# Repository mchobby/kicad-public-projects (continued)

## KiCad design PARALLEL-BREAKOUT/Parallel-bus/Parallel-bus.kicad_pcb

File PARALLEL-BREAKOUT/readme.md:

# Parallel-Breakout retro development project with Linux & Python

## A bit a history

I wanted to re-discover __Parallel port development__ on older computer with Python (see [Dell Optiplex GX260](https://arduino103.blogspot.com/search?q=optiplex) and [HP NC6000](https://arduino103.blogspot.com/search?q=nc6000) salvage).

Those are quite old computers as the OPtiplex is date from 2002 (2007 for the NC6000) and I wanted to used more modern operating system for development.

[Linux Bionic Puppy and Fossa Puppy](https://puppylinux-woof-ce.github.io/) (derivated from Ubuntu Linux) does a really great job to modernise the operating system.

## Browsing sub-projects

This project is made of many sub-project. Just navigates the various sub-folder to gets more information about them. I stored readme files into each sub-folder to give some details about that part of the project.

The main sub-projects are:
* [Parallel-brk](Parallel-brk): breakout a parallel port to a RPi GPIO alike port.
* [Parallel-cobbler](Parallel-cobbler): from GPIO to breadboard converted.  
* [Parallel-bus](Parallel-bus): from GPIO to 16bits address bus + 8bits data bus + clock + control bus.  

# Prototyping Hardware
From there, I started to design 2 first boards to facilitate test and prototyping.

The board are shares in the following sub-directories, __please keep the credit__:

* [Parallel-brk](Parallel-brk) : breakouts the Parallel port to a 2x20 connector (like Raspberry-Pi) and inject 3.3 + 5V at the right place on the GPIOs
* [Parallel-cobbler](Parallel-cobbler) : translate the 2x20 pinout to a prototyping Cobbler. Cobbler  a board that can be plugged onto a breadboard to make prototyping. The 5V and 3.3V are also available on the breakout so we are ready to prototype stuff!

__/!\ 5V Logic /!\__ warning the parallel port is 5V logic only!

## Installing pyparallel

Developping parallel port stuff with Python would requires to install the `pyparallel` package.

We have described the __python3-parallel__ (0.2.2-2) ["Linux Package Installation" in this article](https://arduino103.blogspot.com/2022/06/recuperation-dell-optiplex-gx260n-et_01622143827.html) to support PyParallel on my Linux Puppy (still written in french, ask google for translation)

## Inital Input/Output test

The article "[Parallel Breakout: test d'entrée/sortie en python](https://arduino103.blogspot.com/2022/07/parallel-breakout-tests-dentreesorties.html)" (Google may help to translate) shows how to wire input and outpout on the breakout and how to drive them from Python.

The Parallel port do have 8 output data bit (D0..D7).

The parallel port also brings 5 inputs bits and 4 additional output bits (C0..C4 that can be switched to input... but not recommended).

The Python code is [available here](https://arduino103.blogspot.com/2022/07/parallel-breakout-tests-dentreesorties.html).

# Expand parallel port to data & address bus

Read more from the [Parallel-bus sub-project folder](Parallel-bus/)

# Ressources
* [All the "Parallel-Breakout" articles available on the blog](https://arduino103.blogspot.com/search?q=parallel-breakout) (_french_)

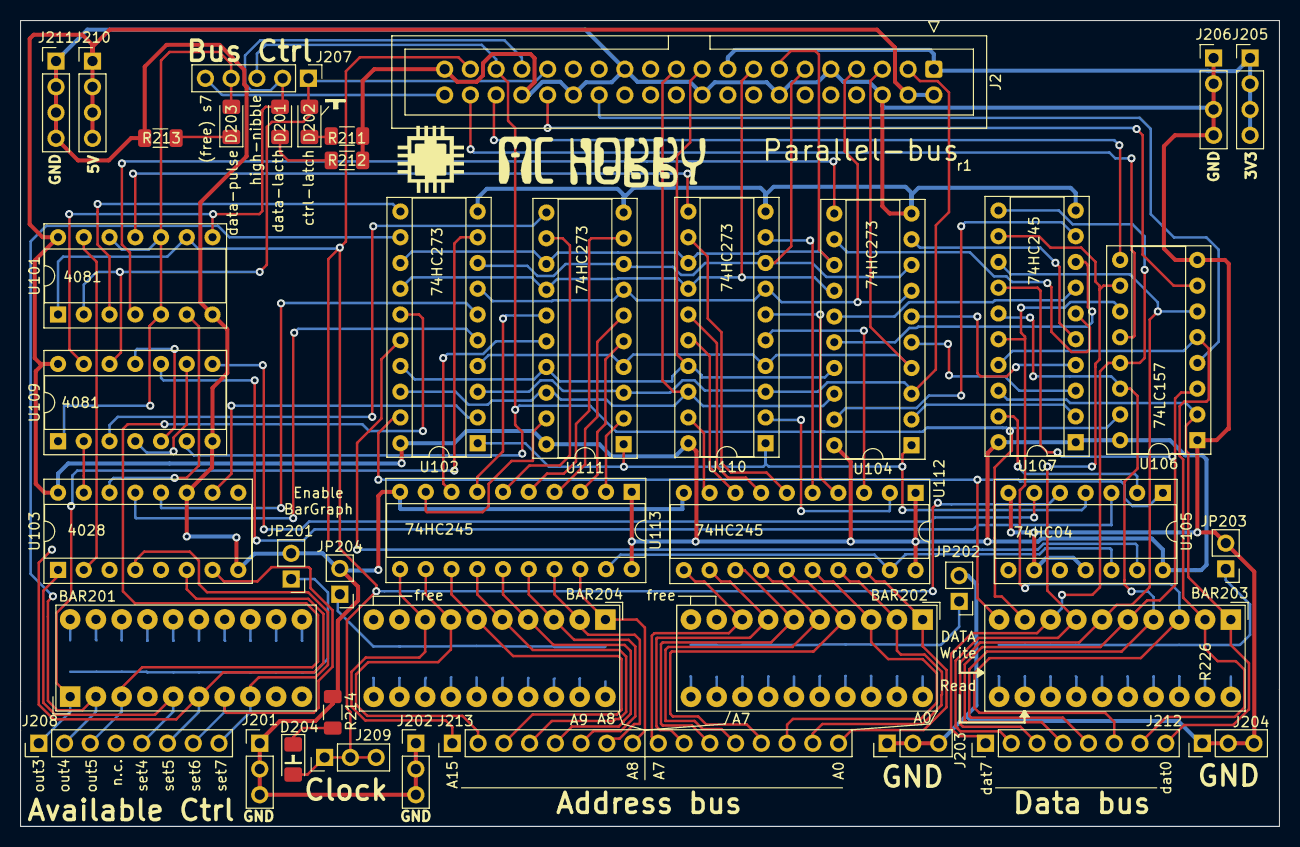
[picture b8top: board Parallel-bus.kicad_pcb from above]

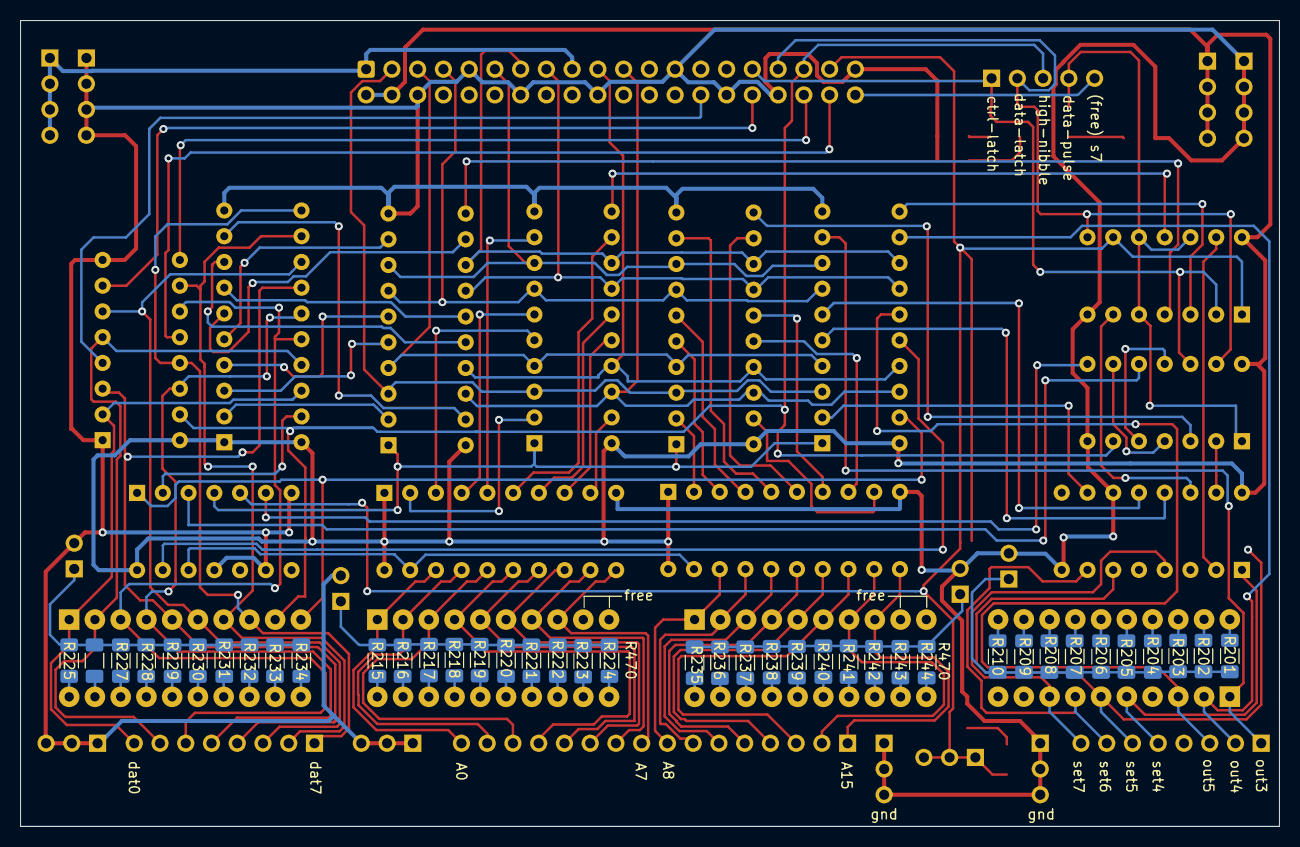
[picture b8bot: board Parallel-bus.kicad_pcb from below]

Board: 2 copper layers, 124.2 x 79.5 mm, 82 parts (40 on the bottom side), 143 nets.

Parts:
BAR201: Bar_Avail_bits; HDSP-4830
BAR202: Bar_Addr_L; HDSP-4830
BAR203: Bar_Data_bus; HDSP-4830
BAR204: Bar_Addr_H; HDSP-4830
D201: LED_Data_Latch; LED_1206_3216Metric_Pad1.42x1.75mm_HandSolder
D202: LED_Ctrl_Latch; LED_1206_3216Metric_Pad1.42x1.75mm_HandSolder
D203, D204: LED_Data_Pulse; LED_1206_3216Metric_Pad1.42x1.75mm_HandSolder
J2: Conn_RASP; IDC-Header_2x20_P2.54mm_Vertical
J201: Conn_GND0; PinHeader_1x03_P2.54mm_Vertical
J202: Conn_GND1; PinHeader_1x03_P2.54mm_Vertical
J203: Conn_GND2; PinHeader_1x03_P2.54mm_Vertical
J204: Conn_GND3; PinHeader_1x03_P2.54mm_Vertical
J205: Conn_3V; PinHeader_1x04_P2.54mm_Vertical
J206: Conn_GND4; PinHeader_1x04_P2.54mm_Vertical
J207: Conn_Bus_Ctrl; PinHeader_1x05_P2.54mm_Vertical
J208: Conn_Avail_Ctrl; PinHeader_1x08_P2.54mm_Vertical
J209: Conn_clock; PinHeader_1x03_P2.54mm_Vertical
J210: Conn_5V; PinHeader_1x04_P2.54mm_Vertical
J211: Conn_GND5; PinHeader_1x04_P2.54mm_Vertical
J212: Conn_Data_bus; PinHeader_1x08_P2.54mm_Vertical
J213: Conn_Addr_bus; PinHeader_1x16_P2.54mm_Vertical
JP201, JP203: Jumper; PinHeader_1x02_P2.54mm_Vertical
JP202: Addr-L; PinHeader_1x02_P2.54mm_Vertical
JP204: Addr-H; PinHeader_1x02_P2.54mm_Vertical
R201, R202, R203, R204, R205, R206, R207, R208, R209, R210, R211, R212, R213, R214, R215, R216, R217, R218, R219, R220, R221, R222, R223, R224, R225, R226, R227, R228, R229, R230, R231, R232, R233, R234, R235, R236, R237, R238, R239, R240, R241, R242, R243, R244: R470; R_1206_3216Metric_Pad1.30x1.75mm_HandSolder
U101, U109: 4081; DIP-14_W7.62mm_Socket
U102, U104, U110, U111: 74HC273; DIP-20_W7.62mm_Socket
U103: 4028; DIP-16_W7.62mm_Socket
U105: 74HC04; DIP-14_W7.62mm_Socket
U106: 74LS157; DIP-16_W7.62mm_Socket
U107, U112, U113: 74HC245; DIP-20_W7.62mm_Socket

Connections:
+3V3: J2.1, J2.17, J205.1, J205.2, J205.3, J205.4
+5V: J2.2, J2.4, J210.1, J210.2, J210.3, J210.4, U101.14, U102.20, U103.16, U104.20, U105.14, U106.16, U107.1, U107.20, U109.14, U110.20, U111.20, U112.1, U112.20, U113.1, U113.20
/addr-h-set: U103.15, U109.2
/addr-l-set: U101.13, U103.2
/addr-out: U102.16, U105.13
/d0: J2.3, U102.3, U104.3, U110.3, U111.3
/d1: J2.5, U102.4, U104.4, U110.4, U111.4
/d2: J2.7, U102.7, U104.7, U110.7, U111.7
/d3: J2.11, U102.8, U104.8, U110.8, U111.8
/d4: J2.13, U102.13, U104.13, U110.13, U111.13
/d5: J2.15, U102.14, U104.14, U110.14, U111.14
/d6: J2.19, U102.17, U104.17, U110.17, U111.17
/d7: J2.21, U102.18, U104.18, U110.18, U111.18
/data-set: U101.6, U103.14
/s3: J2.28, U106.4
/s4: J2.32, U106.7
/s5: J2.36, U106.9
/s6: J2.38, U106.12
GND: J2.6, J2.9, J2.14, J2.20, J2.25, J2.30, J2.34, J2.39, J201.1, J201.2, J201.3, J202.1, J202.2, J202.3, J203.1, J203.2, J203.3, J204.1, J204.2, J204.3, J206.1, J206.2, J206.3, J206.4, J211.1, J211.2, J211.3, J211.4, JP201.2, JP202.2, JP203.2, JP204.2, R211.1, R212.1, R213.1, R214.1, U101.7, U102.10, U103.8, U103.11, U104.10, U105.7, U105.9, U105.11, U106.1, U106.8, U107.10, U109.7, U110.10, U111.10, U112.10, U113.10
unnamed: BAR201.11, R210.2
unnamed: BAR201.12, R209.2
unnamed: BAR201.13, R208.2
unnamed: BAR201.14, R207.2
unnamed: BAR201.15, R206.2
unnamed: BAR201.16, R205.2
unnamed: BAR201.17, R204.2
unnamed: BAR201.18, R203.2
unnamed: BAR201.19, R202.2
unnamed: BAR201.20, R201.2
unnamed: BAR202.11, R224.2
unnamed: BAR202.12, R223.2
unnamed: BAR202.13, R222.2
unnamed: BAR202.14, R221.2
unnamed: BAR202.15, R220.2
unnamed: BAR202.16, R219.2
unnamed: BAR202.17, R218.2
unnamed: BAR202.18, R217.2
unnamed: BAR202.19, R216.2
unnamed: BAR202.20, R215.2
unnamed: BAR203.11, R234.2
unnamed: BAR203.12, R233.2
unnamed: BAR203.13, R232.2
unnamed: BAR203.14, R231.2
unnamed: BAR203.15, R230.2
unnamed: BAR203.16, R229.2
unnamed: BAR203.17, R228.2
unnamed: BAR203.18, R227.2
unnamed: BAR203.19, R226.2
unnamed: BAR203.20, R225.2
unnamed: BAR204.11, R244.2
unnamed: BAR204.12, R243.2
unnamed: BAR204.13, R242.2
unnamed: BAR204.14, R241.2
unnamed: BAR204.15, R240.2
unnamed: BAR204.16, R239.2
unnamed: BAR204.17, R238.2
unnamed: BAR204.18, R237.2
unnamed: BAR204.19, R236.2
unnamed: BAR204.20, R235.2
unnamed: D201.1, R212.2
unnamed: D202.1, R211.2
unnamed: D203.1, R213.2
unnamed: D204.1, R214.2
unnamed: JP201.1, R201.1, R202.1, R203.1, R204.1, R205.1, R206.1, R207.1, R208.1, R209.1, R210.1
unnamed: JP202.1, R215.1, R216.1, R217.1, R218.1, R219.1, R220.1, R221.1, R222.1, R223.1, R224.1
unnamed: JP203.1, R225.1, R226.1, R227.1, R228.1, R229.1, R230.1, R231.1, R232.1, R233.1, R234.1
unnamed: JP204.1, R235.1, R236.1, R237.1, R238.1, R239.1, R240.1, R241.1, R242.1, R243.1, R244.1
unnamed: U101.3, U102.11
unnamed: U101.4, U104.11
unnamed: U101.11, U110.11
unnamed: U102.2, U103.10
unnamed: U102.5, U103.13
unnamed: U102.6, U103.12
unnamed: U104.2, U107.2
unnamed: U104.5, U107.3
unnamed: U104.6, U107.4
unnamed: U104.9, U107.5
unnamed: U104.12, U107.6
unnamed: U104.15, U107.7
unnamed: U104.16, U107.8
unnamed: U104.19, U107.9
unnamed: U105.2, U107.19
unnamed: U105.3, U109.10
unnamed: U105.6, U109.8
unnamed: U105.12, U112.19, U113.19
unnamed: U109.3, U111.11
unnamed: U109.4, U109.9
unnamed: U109.5, U109.11
unnamed: U110.2, U112.2
unnamed: U110.5, U112.3
unnamed: U110.6, U112.4
unnamed: U110.9, U112.5
unnamed: U110.12, U112.6
unnamed: U110.15, U112.7
unnamed: U110.16, U112.8
unnamed: U110.19, U112.9
unnamed: U111.2, U113.2
unnamed: U111.5, U113.3
unnamed: U111.6, U113.4
unnamed: U111.9, U113.5
unnamed: U111.12, U113.6
unnamed: U111.15, U113.7
unnamed: U111.16, U113.8
unnamed: U111.19, U113.9
adr0: BAR202.1, J213.16, U112.18
adr1: BAR202.2, J213.15, U112.17
adr2: BAR202.3, J213.14, U112.16
adr3: BAR202.4, J213.13, U112.15
adr4: BAR202.5, J213.12, U112.14
adr5: BAR202.6, J213.11, U112.13
adr6: BAR202.7, J213.10, U112.12
adr7: BAR202.8, J213.9, U112.11
adr8: BAR204.1, J213.8, U113.18
adr9: BAR204.2, J213.7, U113.17
adr10: BAR204.3, J213.6, U113.16
adr11: BAR204.4, J213.5, U113.15
adr12: BAR204.5, J213.4, U113.14
adr13: BAR204.6, J213.3, U113.13
adr14: BAR204.7, J213.2, U113.12
adr15: BAR204.8, J213.1, U113.11
clock: D204.2, J2.37, J209.1, J209.2, J209.3, U101.1, U101.9, U105.5
ctrl-latch: D202.2, J2.31, J207.1, U101.2, U109.12
dat0: BAR203.1, J212.8, U106.2, U107.18
dat1: BAR203.2, J212.7, U106.5, U107.17
dat2: BAR203.3, J212.6, U106.11, U107.16
dat3: BAR203.4, J212.5, U106.14, U107.15
dat4: BAR203.5, J212.4, U106.3, U107.14
dat5: BAR203.6, J212.3, U106.6, U107.13
dat6: BAR203.7, J212.2, U106.10, U107.12
dat7: BAR203.8, J212.1, U106.13, U107.11
data-latch: D201.2, J2.33, J207.2, U101.8, U109.13
data-out: BAR203.10, U102.19, U105.1
data-pulse: D203.2, J207.4, U101.5, U101.10, U101.12, U109.1
high-nibble: BAR203.9, J2.35, J207.3, U106.15, U109.6
nReset: U102.1, U104.1, U105.4, U110.1, U111.1
out3: BAR201.1, J208.1, U102.9
out4: BAR201.2, J208.2, U102.12
out5: BAR201.3, J208.3, U102.15
s7: J2.40, J207.5
set4: BAR201.5, J208.5, U103.1
set5: BAR201.6, J208.6, U103.6
set6: BAR201.7, J208.7, U103.7
set7: BAR201.8, J208.8, U103.4

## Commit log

2021-12-02 Open Hardware logo
2021-12-02 setup gitignore
2021-12-02 Add PICO-BOUNCING-LED
2021-12-02 fix image
2022-08-08 Parallel-Breakout: initial commit
2022-08-15 Parallel-Bus: initial design
2022-08-15 add missing project files
2023-06-07 initial append of HASKEL-Z80 CPU-Board
2023-06-18 HASKEL-Z80 add-on board & GLS27SF512 to DIP28
2023-06-18 CPU-AddOn documentation folder
2023-06-26 Programmer GLS27SF512
2023-06-26 addition info on other project
2023-07-17 update projects
2023-07-18 Update programmer
2023-07-23 EEPROM Programmer r5
2023-10-22 First assembly example with CPU-BOARD-AddOn
2023-10-22 z80asm add manpage documentation
2023-10-27 Z80-ASM: PIO output example
2023-10-29 PIO in input mode
2023-11-06 stack pointer
2023-11-20 Z80-ASM test and examples
2024-08-17 SuperPi ressources
2025-04-09 Adding Pyboard-to-Zumo adapter board
